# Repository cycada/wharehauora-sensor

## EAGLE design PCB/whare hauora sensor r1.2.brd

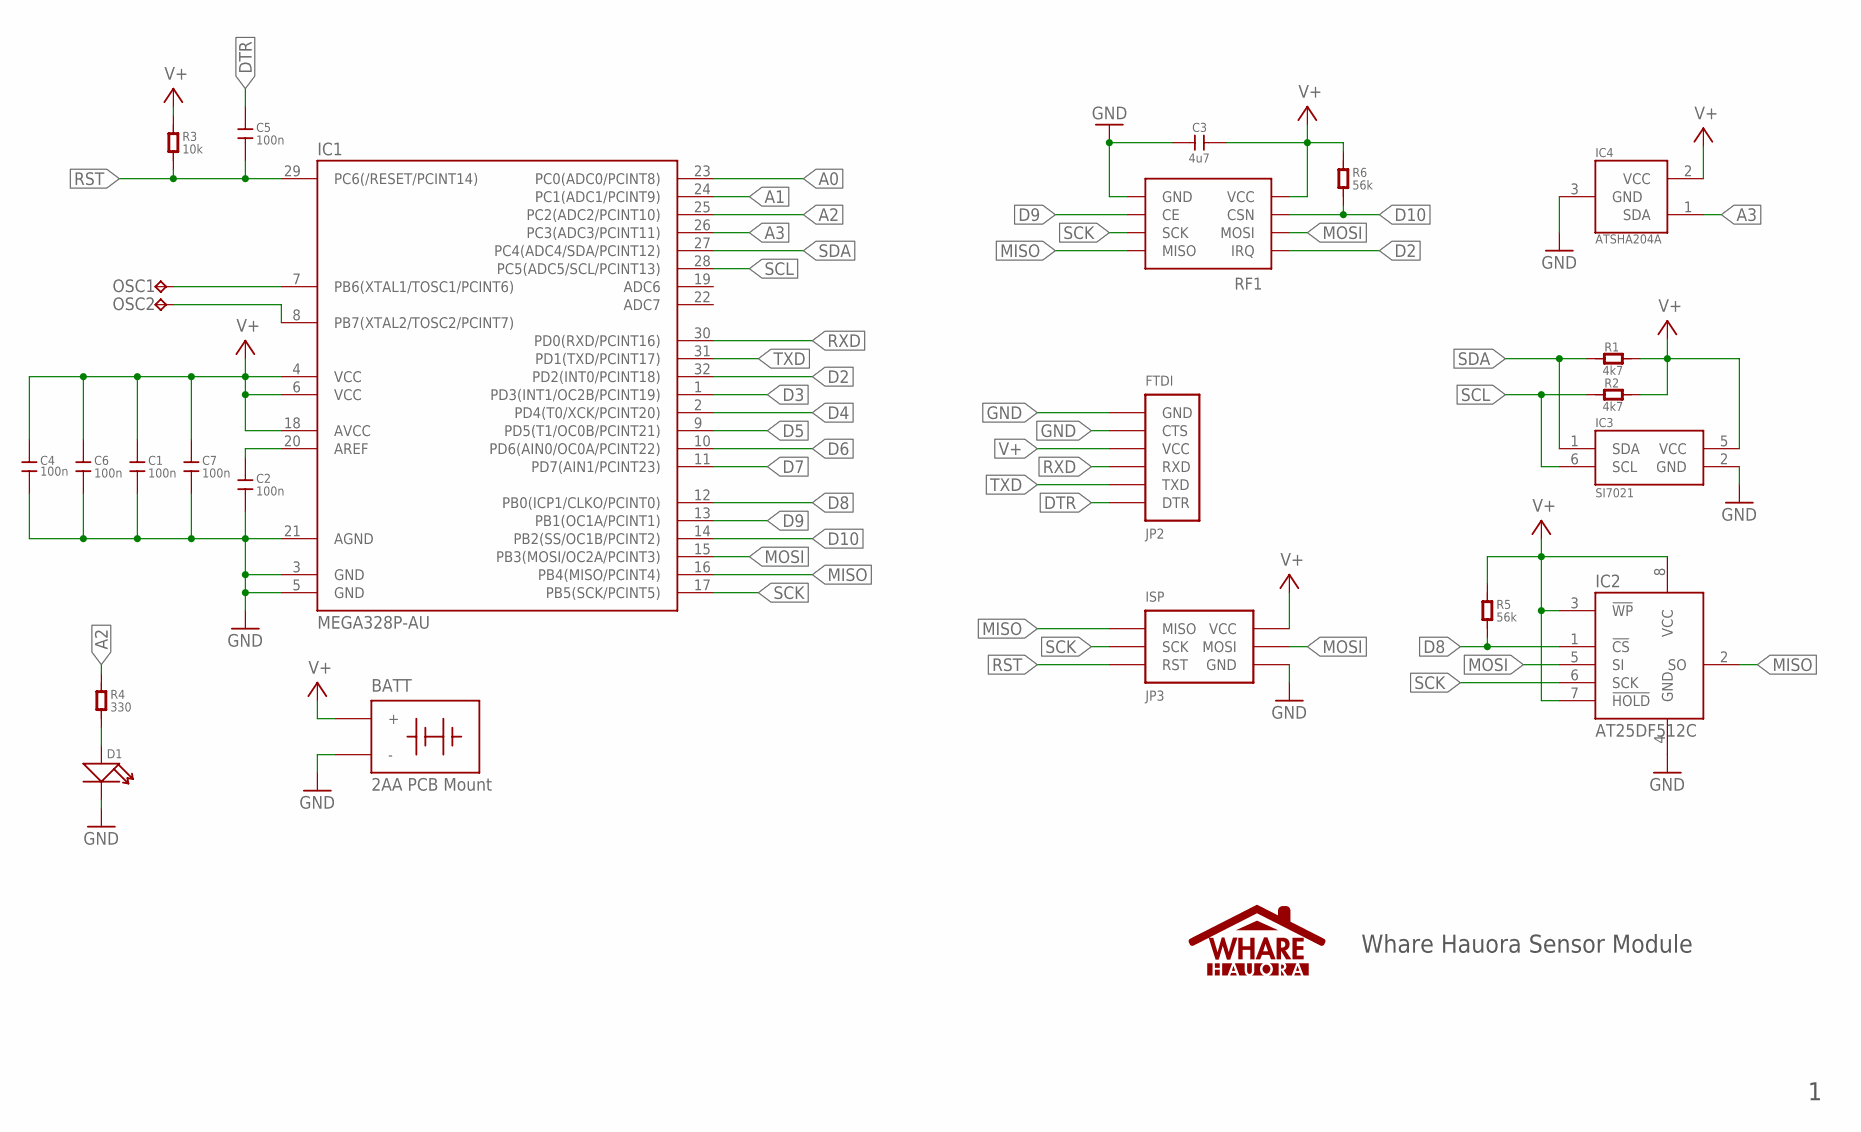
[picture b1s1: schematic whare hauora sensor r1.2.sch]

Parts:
BATT: 2AA-PACK; 2AA-PACK\
C1, C2, C4, C5, C6, C7: 100n; C0603
C3: 4u7; C0603
D1: LED-0603
IC1: MEGA328P-AU; TQFP32-08
IC2: AT25DF512C; SO8
IC3: SI7021; DFN6
IC4: ATSHA204A; SOT23
JP2: FTDI
JP3: ISP
OSC1, OSC2: TPTP10R; TP10R
R1, R2: 4k7; R0603
R3: 10k; R0603
R4: 330; R0603
R5, R6: 56k; R0603
RF1: NRF24L01+

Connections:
A0: IC1.23 (PC0(ADC0/PCINT8))
A1: IC1.24 (PC1(ADC1/PCINT9))
A2: IC1.25 (PC2(ADC2/PCINT10)), R4.1
A3: IC1.26 (PC3(ADC3/PCINT11)), IC4.1 (SDA)
D2: IC1.32 (PD2(INT0/PCINT18)), RF1.P$8 (IRQ)
D3: IC1.1 (PD3(INT1/OC2B/PCINT19))
D4: IC1.2 (PD4(T0/XCK/PCINT20))
D5: IC1.9 (PD5(T1/OC0B/PCINT21))
D6: IC1.10 (PD6(AIN0/OC0A/PCINT22))
D7: IC1.11 (PD7(AIN1/PCINT23))
D8: IC1.12 (PB0(ICP1/CLKO/PCINT0)), IC2.1 (!CS), R5.1
D9: IC1.13 (PB1(OC1A/PCINT1)), RF1.P$3 (CE)
D10: IC1.14 (PB2(SS/OC1B/PCINT2)), R6.1, RF1.P$4 (CSN)
DTR: C5.1, JP2.DTR
GND: BATT.-, C1.2, C2.2, C3.1, C4.2, C6.2, C7.2, D1.-, IC1.3 (GND), IC1.5 (GND), IC1.21 (AGND), IC2.4 (GND), IC3.2 (GND), IC4.3 (GND), JP2.CTS, JP2.GND, JP3.GND, RF1.P$1 (GND)
MISO: IC1.16 (PB4(MISO/PCINT4)), IC2.2 (SO), JP3.MISO, RF1.P$7 (MISO)
MOSI: IC1.15 (PB3(MOSI/OC2A/PCINT3)), IC2.5 (SI), JP3.MOSI, RF1.P$6 (MOSI)
unnamed: IC1.7 (PB6(XTAL1/TOSC1/PCINT6)), OSC1.TP
unnamed: IC1.8 (PB7(XTAL2/TOSC2/PCINT7)), OSC2.TP
unnamed: D1.+, R4.2
unnamed: C2.1, IC1.20 (AREF)
RST: C5.2, IC1.29 (PC6(/RESET/PCINT14)), JP3.RST, R3.1
RXD: IC1.30 (PD0(RXD/PCINT16)), JP2.RXD
SCK: IC1.17 (PB5(SCK/PCINT5)), IC2.6 (SCK), JP3.SCK, RF1.P$5 (SCK)
SCL: IC1.28 (PC5(ADC5/SCL/PCINT13)), IC3.6 (SCL), R2.1
SDA: IC1.27 (PC4(ADC4/SDA/PCINT12)), IC3.1 (SDA), R1.1
TXD: IC1.31 (PD1(TXD/PCINT17)), JP2.TXD
V+: BATT.+, C1.1, C3.2, C4.1, C6.1, C7.1, IC1.4 (VCC), IC1.6 (VCC), IC1.18 (AVCC), IC2.3 (!WP), IC2.7 (!HOLD), IC2.8 (VCC), IC3.5 (VCC), IC4.2 (VCC), JP2.VCC, JP3.VCC, R1.2, R2.2, R3.2, R5.2, R6.2, RF1.P$2 (VCC)

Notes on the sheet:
Whare Hauora Sensor Module

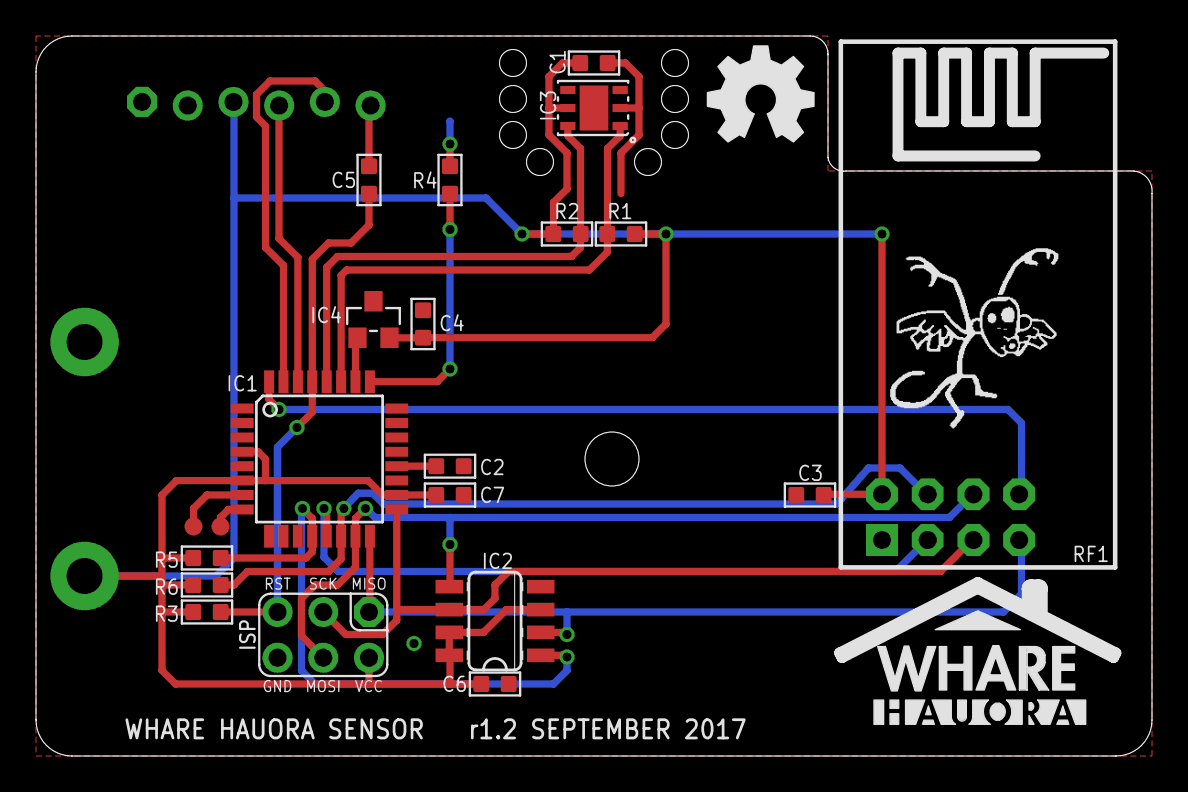
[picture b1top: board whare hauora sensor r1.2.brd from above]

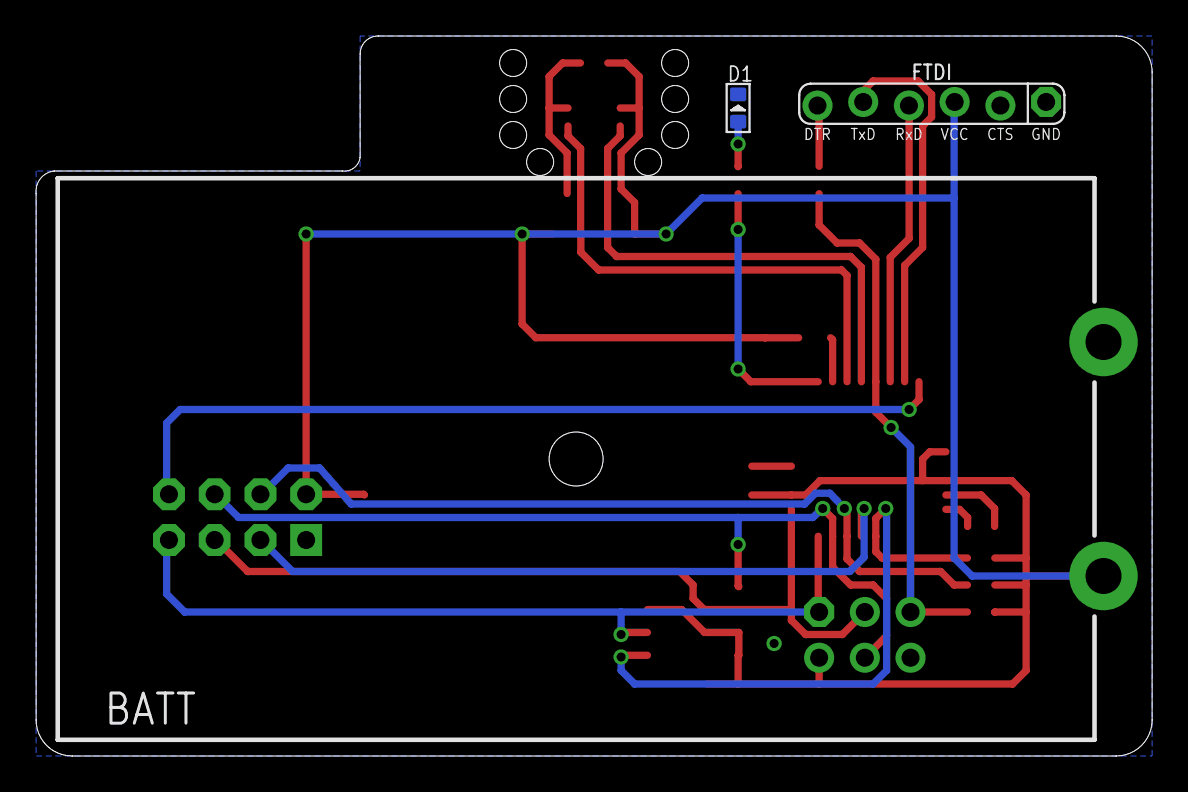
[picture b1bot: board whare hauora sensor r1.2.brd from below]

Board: 2 copper layers, 62.0 x 40.0 mm, 27 parts (3 on the bottom side), 21 nets.

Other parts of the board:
U$1: OSHW-LOGO
U$2: WHAREHAUORA-SMALL
U$3: MONKEY

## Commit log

2017-09-08 Revision 1.2
    Revised layout for assembly into a case. Can still be used as stand alone
    Clearing PCB away from antenna area.
